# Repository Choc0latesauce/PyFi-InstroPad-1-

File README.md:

# InstroPad(1)
It's time to make some noise!

## DISCLAIMER ⚠️
I can't believe I have to put this but people always seem to think my writing is AI lol, it isn't, I wrote this all myself!!

## The Pitch
Do you like listening to music? - Most likely.  
Do you wanna make music?? - Surely.  
Don't wanna drop your life's savings on a synth that does but one thing?  
Then you need InstroPad(1)! My fully custom music creation tool and macro pad.

## The Features
- OLED display
- Rotary + push button encoder - for all your knobby interface needs
- 3x3 fully customisable pad layout - that's 9 whole pads!
- Inspired by classics such as the TR 808 and 303
- Full portability - make music anywhere!
- Fully custom firmware
- Fully custom software - coming soon(tm)
- Specifically designed M3 mounting holes that allow for adjustments in accordance to manufacturing tolerances
- Standard numpad inputs - the switches act as a numpad 1-9 and the push encoder acts as an enter, how useful!

## What I've learnt:
- PCB design
- CAD software
- Video editing
- Schematic design
- PCB routing

## Software I used
- Fusion 360
- Kicad
- QMK MSYS

## BOM - **Prices TBC**
- 9x Cherry MX Switches
- 9x Blank DSA Keycaps
- 1x XIAO RP2040
- 6x M3 Heatset
- 6x M3x16 Bolt
- 1x EC11E Encoder
- 0.91 Inch OLED display

## Notes:
- I will finish the synth software when I actually assemble InstroPad(1)

## The Gallery

<3

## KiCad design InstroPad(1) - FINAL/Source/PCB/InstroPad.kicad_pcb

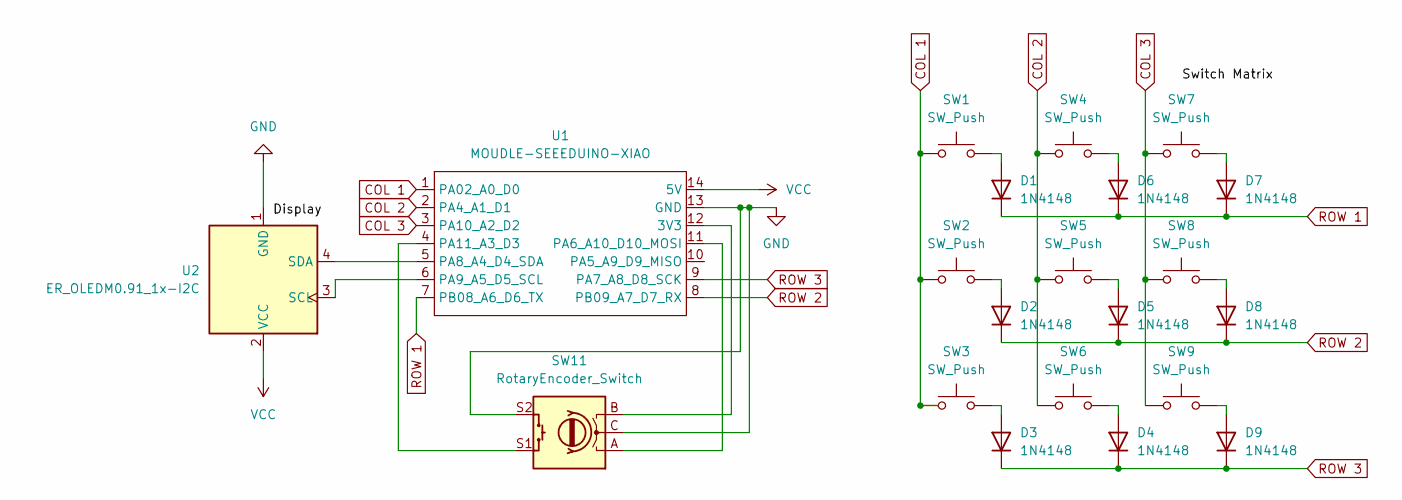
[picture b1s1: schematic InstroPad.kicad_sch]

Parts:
D1, D2, D3, D4, D5, D6, D7, D8, D9: 1N4148; D_DO-35_SOD27_P7.62mm_Horizontal
SW1, SW2, SW3, SW4, SW5, SW6, SW7, SW8, SW9: SW_Push; SW_Cherry_MX_1.00u_PCB
SW11: RotaryEncoder_Switch; RotaryEncoder_Alps_EC11E-Switch_Vertical_H20mm
U1: MOUDLE-SEEEDUINO-XIAO; XIAO-Generic-Hybrid-14P-2.54-21X17.8MM
U2: ER_OLEDM0.91_1x-I2C

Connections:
COL 1: SW1.1, SW2.1, SW3.1, U1.1 (PA02_A0_D0)
COL 2: SW4.1, SW5.1, SW6.1, U1.2 (PA4_A1_D1)
COL 3: SW7.1, SW8.1, SW9.1, U1.3 (PA10_A2_D2)
GND: SW11.C, SW11.S2, U1.13 (GND), U2.1 (GND)
unnamed: D1.2 (A), SW1.2
unnamed: D2.2 (A), SW2.2
unnamed: D3.2 (A), SW3.2
unnamed: D4.2 (A), SW6.2
unnamed: D5.2 (A), SW5.2
unnamed: D6.2 (A), SW4.2
unnamed: D7.2 (A), SW7.2
unnamed: D8.2 (A), SW8.2
unnamed: D9.2 (A), SW9.2
unnamed: SW11.B, U1.12 (3V3)
unnamed: SW11.A, U1.11 (PA6_A10_D10_MOSI)
unnamed: U1.5 (PA8_A4_D4_SDA), U2.4 (SDA)
unnamed: U1.6 (PA9_A5_D5_SCL), U2.3 (SCL)
unnamed: SW11.S1, U1.4 (PA11_A3_D3)
ROW 1: D1.1 (K), D6.1 (K), D7.1 (K), U1.7 (PB08_A6_D6_TX)
ROW 2: D2.1 (K), D5.1 (K), D8.1 (K), U1.8 (PB09_A7_D7_RX)
ROW 3: D3.1 (K), D4.1 (K), D9.1 (K), U1.9 (PA7_A8_D8_SCK)
VCC: U1.14 (5V), U2.2 (VCC)

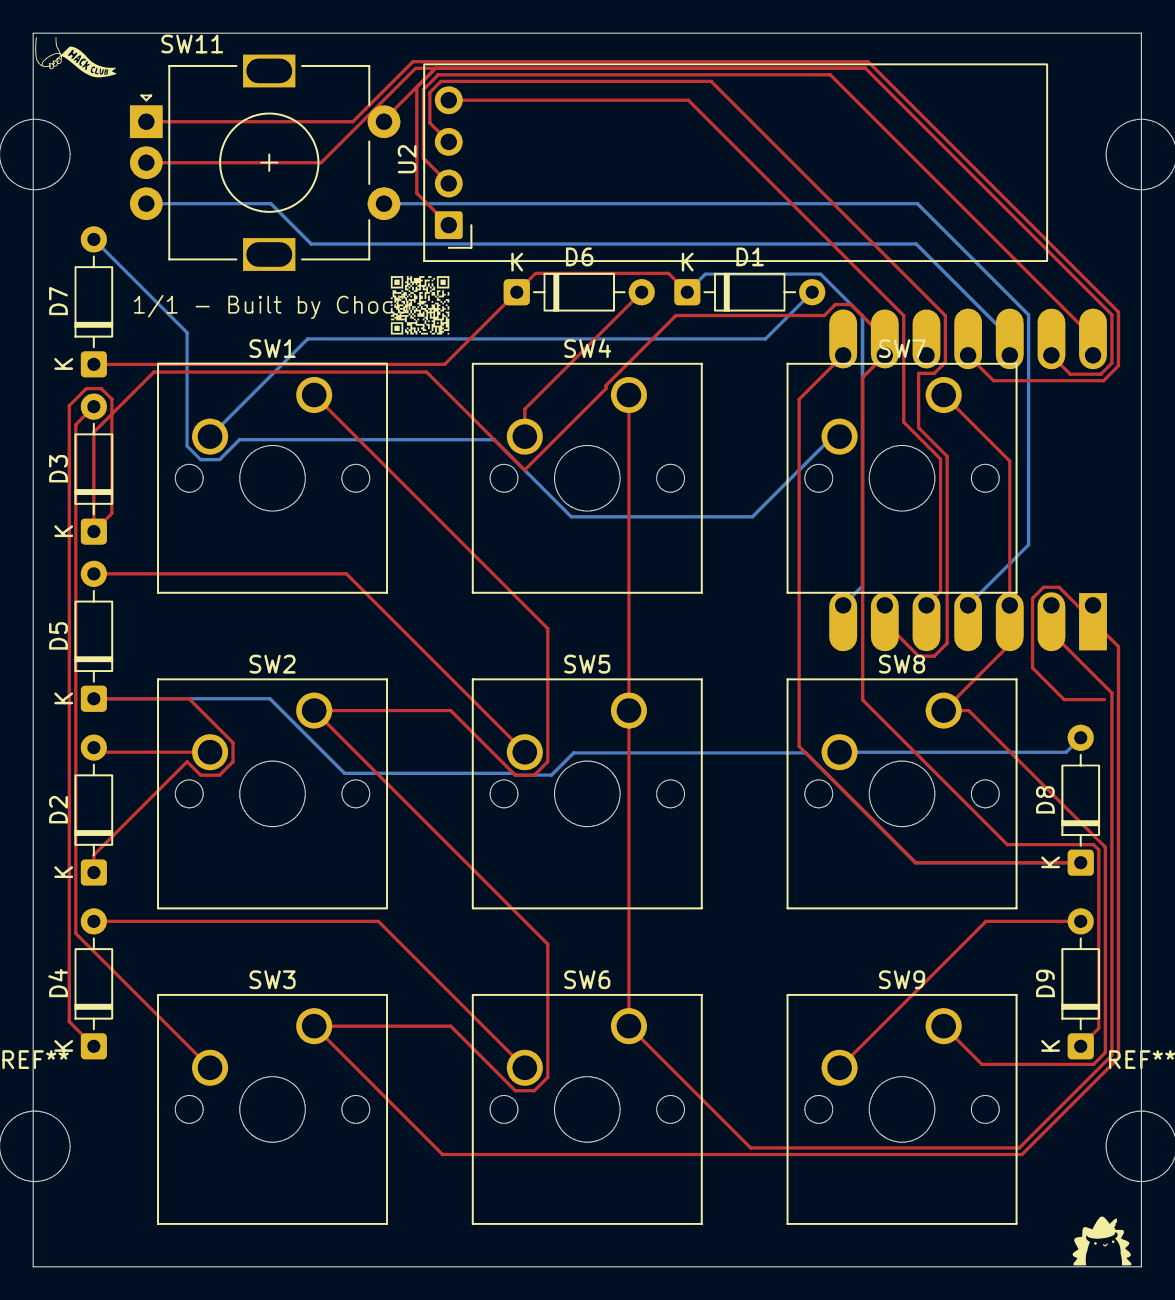
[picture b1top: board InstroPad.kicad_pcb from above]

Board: 2 copper layers, 67.6 x 75.2 mm, 22 parts (1 on the bottom side), 22 nets.

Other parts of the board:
1/1 - Built by Choc0: Untitled_1
